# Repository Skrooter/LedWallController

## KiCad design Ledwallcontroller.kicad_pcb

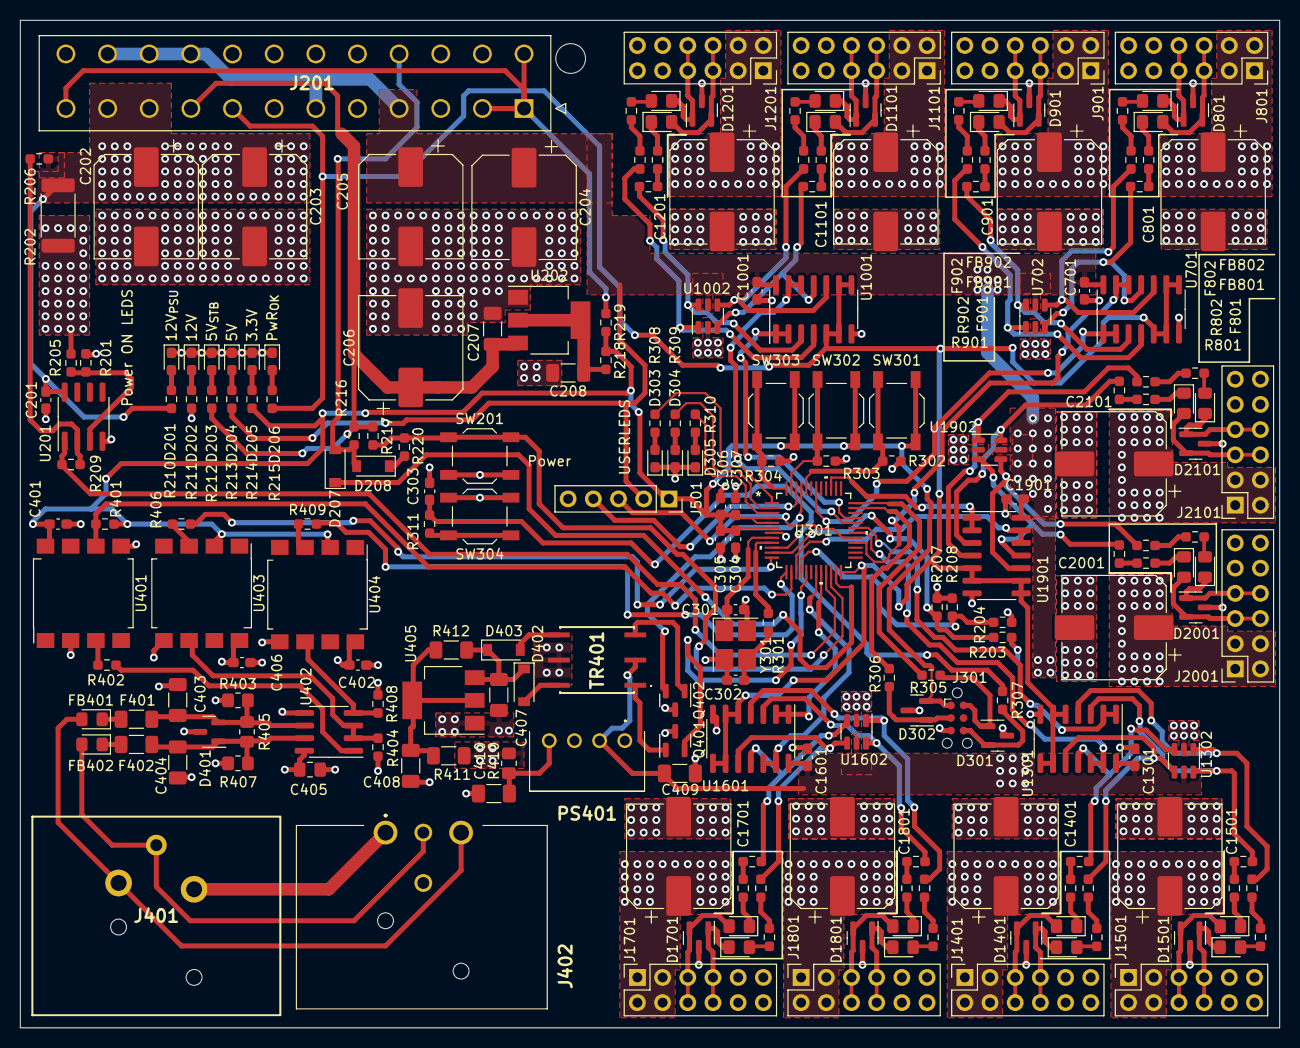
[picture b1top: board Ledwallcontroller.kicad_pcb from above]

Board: 4 copper layers, 127.0 x 101.6 mm, 216 parts (0 on the bottom side), 162 nets.

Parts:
C201, C303, C305, C307, C401, C402, C406, C701, C1001, C1301, C1601, C1901: 100n/50V; C_0603_1608Metric_Pad1.08x0.95mm_HandSolder
C202, C203, C204, C205, C206, C801, C901, C1101, C1201, C1401, C1501, C1701, C1801, C2001, C2101: 220u/50V; CP_Elec_10x10
C207, C208, C407, C408: 22u/25V; C_1206_3216Metric_Pad1.33x1.80mm_HandSolder
C301, C302: 10p/50V; C_0603_1608Metric_Pad1.08x0.95mm_HandSolder
C304: 4u7/16V; C_0603_1608Metric_Pad1.08x0.95mm_HandSolder
C306: 1u/50V; C_0603_1608Metric_Pad1.08x0.95mm_HandSolder
C403, C404: 100p/1kV; C_1206_3216Metric_Pad1.33x1.80mm_HandSolder
C405: 2.2u/50V; C_0805_2012Metric_Pad1.18x1.45mm_HandSolder
C409, C410: 47u/10V; C_1206_3216Metric_Pad1.33x1.80mm_HandSolder
D201, D202, D203, D204, D205, D206: Green; LED_0603_1608Metric_Pad1.05x0.95mm_HandSolder
D207, D208: D; D_SOD-123
D301, D302, D401, D801, D901, D1101, D1201, D1401, D1501, D1701, D1801, D2001, D2101: SM712; SOT-23
D303, D304, D305: Blue; LED_0603_1608Metric_Pad1.05x0.95mm_HandSolder
D402, D403: B5819W; D_SOD-123
F401, F402: Polyfuse_Small; R_1206_3216Metric_Pad1.30x1.75mm_HandSolder
F801, F802, F901, F902, F1101, F1102, F1201, F1202, F1401, F1402, F1501, F1502, F1701, F1702, F1801, F1802, F2001, F2002, F2101, F2102: Polyfuse_Small; R_0603_1608Metric_Pad0.98x0.95mm_HandSolder
FB401, FB402, FB801, FB802, FB901, FB902, FB1101, FB1102, FB1201, FB1202, FB1401, FB1402, FB1501, FB1502, FB1701, FB1702, FB1801, FB1802, FB2001, FB2002, FB2101, FB2102: FerriteBead; D_0805_2012Metric_Pad1.15x1.40mm_HandSolder
J201: ATX-24; 442060007
J301: TC-2030-NL; Tag-Connect_TC2030-IDC-NL_2x03_P1.27mm_Vertical
J401: DMX_{IN}; NC3FAAH0
J402: DMX_{THRU}; NC3MAAH0
J501: Conn_01x06; PinSocket_1x05_P2.54mm_Vertical
J801, J901, J1101, J1201, J1401, J1501, J1701, J1801, J2001, J2101: Conn_02x06_Odd_Even; PinSocket_2x06_P2.54mm_Vertical
PS401: B0505S-1WR3; B0505SW2R2
Q401, Q402: AO3400A; SOT-23
R201, R209: 300k; R_0603_1608Metric_Pad0.98x0.95mm_HandSolder
R202: 10m; R_2512_6332Metric_Pad1.40x3.35mm_HandSolder
R203, R205, R206, R208: 10k; R_0603_1608Metric_Pad0.98x0.95mm_HandSolder
R204: 30k; R_0603_1608Metric_Pad0.98x0.95mm_HandSolder
R207: 15k; R_0603_1608Metric_Pad0.98x0.95mm_HandSolder
R210, R211, R302, R303, R304, R311: 2k2; R_0603_1608Metric_Pad0.98x0.95mm_HandSolder
R212, R213, R215: 820R; R_0603_1608Metric_Pad0.98x0.95mm_HandSolder
R214, R308, R309, R310, R401, R404, R408: 470R; R_0603_1608Metric_Pad0.98x0.95mm_HandSolder
R216, R217: 4k7; R_0603_1608Metric_Pad0.98x0.95mm_HandSolder
R218: 0R; R_0603_1608Metric_Pad0.98x0.95mm_HandSolder
R219, R220: 0R/NM; R_0603_1608Metric_Pad0.98x0.95mm_HandSolder
R301, R305, R306, R307, R801, R802, R901, R902, R1101, R1102, R1201, R1202, R1401, R1402, R1501, R1502, R1701, R1702, R1801, R1802, R2001, R2002, R2101, R2102: 22R; R_0603_1608Metric_Pad0.98x0.95mm_HandSolder
R402: 330R; R_0603_1608Metric_Pad0.98x0.95mm_HandSolder
R403, R407: 680R; R_0805_2012Metric_Pad1.20x1.40mm_HandSolder
R405: 100R/NM; R_0805_2012Metric_Pad1.20x1.40mm_HandSolder
R406, R409: 220R; R_0603_1608Metric_Pad0.98x0.95mm_HandSolder
R410: 0R; R_0805_2012Metric_Pad1.20x1.40mm_HandSolder
R411, R412: 0R/NM; R_1206_3216Metric_Pad1.30x1.75mm_HandSolder
SW201: NM; SW_SPST_TL3342
SW301, SW302, SW303, SW304: SW_MEC_5G; SW_SPST_TL3342
TR401: VPT85BB-01A; VPT85BB01A
U201: OPA2197xD; SOIC-8_3.9x4.9mm_P1.27mm
U202: AMS1117-3.3; SOT-223-3_TabPin2
U301: STM32G030C8T6; LQFP48
U401, U403, U404: 6N137; SSO-8_6.7x9.8mm_P2.54mm_Clearance8mm
U402: SN65176B; SOIC-8_3.9x4.9mm_P1.27mm
U405: AMS1117-5.0; SOT-223-3_TabPin2
U701, U1001, U1301, U1601, U1901: 74HC08D; SOIC-14_3.9x8.7mm_P1.27mm
U702, U1002, U1302, U1602, U1902: SRV05-4; SOT-23-6
Y301: 16MHz; Crystal_SMD_3225-4Pin_3.2x2.5mm_HandSoldering

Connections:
+3.3V: C304.1, C305.2, C306.1, C307.1, C401.2, D302.2 (A2), J301.1, J501.1, R214.2, R218.1, R219.2, R401.2, SW301.2 (B), SW302.2 (B), SW303.2 (B), U301.4 (VBAT), U301.5 (VREF+), U301.6 (VDD/VDDA), U401.8 (VCC), U403.2 (A), U404.2 (A)
+5V: C204.1, C205.1, C409.2, C701.1, C1001.1, C1301.1, C1601.1, C1901.1, J201.4 (+5V), J201.6 (+5V), J201.21 (+5V), J201.22 (+5V), J201.23 (+5V), J501.2, PS401.2 (+Vin), R203.2, R213.2, TR401.2, U701.14 (VDD), U702.5 (VP), U1001.14 (VDD), U1002.5 (VP), U1301.14 (VDD), U1302.5 (VP), U1601.14 (VDD), U1602.5 (VP), U1901.14 (VDD), U1902.5 (VP)
+12V: C801.1, C901.1, C1101.1, C1201.1, C1401.1, C1501.1, C1701.1, C1801.1, C2001.1, C2101.1, J801.1, J801.2, J801.3, J801.4, J901.1, J901.2, J901.3, J901.4, J1101.1, J1101.2, J1101.3, J1101.4, J1201.1, J1201.2, J1201.3, J1201.4, J1401.1, J1401.2, J1401.3, J1401.4, J1501.1, J1501.2, J1501.3, J1501.4, J1701.1, J1701.2, J1701.3, J1701.4, J1801.1, J1801.2, J1801.3, J1801.4, J2001.1, J2001.2, J2001.3, J2001.4, J2101.1, J2101.2, J2101.3, J2101.4, R202.1, R204.1, R205.2, R211.2
/5V_{MONITOR}: R203.1, R207.1, U301.11 (PA0)
/12V_{Isense}: R209.2, U201.1, U301.21 (PB2)
/12V_{MONITOR}: R204.2, R208.2, U301.16 (PA5)
/Button_{POWER}: R217.2, R220.1, SW201.1 (A), U301.22 (PB10)
/DMX/AMS1117_{5VOUT}: C408.1, R411.2, R412.2, U405.2 (VO)
/DMX/B0505_{OUTPUT}: C410.1, PS401.4 (+Vout), R410.1
/DMX/BUS_{A}: FB401.2, J401.2, J402.2
/DMX/BUS_{B}: FB402.2, J401.3, J402.3
/DMX/DMX_{A}: C403.1, D401.2 (A2), F401.2, R403.2, R405.1, U402.6 (A)
/DMX/DMX_{B}: C404.2, D401.1 (A1), F402.2, R405.2, R407.2, U402.7 (B)
/DMX/ISO5V_{rectified}: C407.1, D402.1 (K), D403.1 (K), R412.1, U405.3 (VI)
/DMX/ISO_{DE}: R404.2, U402.2 (~RE), U402.3 (DE), U403.6 (VO)
/DMX/ISO_{D}: R408.2, U402.4 (D), U404.6 (VO)
/DMX/ISO_{R}: R402.1, U402.1 (R)
/DMX/ISO_{TRAFO1}: D402.2 (A), TR401.6
/DMX/ISO_{TRAFO2}: D403.2 (A), TR401.4
/DMX/OPTO_{DE}: R406.1, U403.3 (C)
/DMX/OPTO_{TX}: R409.1, U404.3 (C)
/DMX/Trafo1prim: Q401.1 (D), TR401.1
/DMX/Trafo2prim: Q402.1 (D), TR401.3
/DMX/U401_{C}: R402.2, U401.3 (C)
/DMX/filtered_{A}: F401.1, FB401.1
/DMX/filtered_{B}: F402.1, FB402.1
/DMX_{DE}: R406.2, U301.12 (PA1)
/DMX_{RX}: R401.1, U301.14 (PA3), U401.6 (VO)
/DMX_{TX}: R409.2, U301.13 (PA2)
/Enable_Power: D207.1 (K), U301.23 (PB11)
/LEDOUT/LEDOUTCELL0/LEDOUTEDGE_{A}/LEDOUT: R801.1, U701.11, U702.3 (IO2)
/LEDOUT/LEDOUTCELL0/LEDOUTEDGE_{A}/LED_{BEAD}: F801.2, FB801.1
/LEDOUT/LEDOUTCELL0/LEDOUTEDGE_{A}/LED_{CONN}: D801.2 (A2), FB801.2, J801.5, J801.6
/LEDOUT/LEDOUTCELL0/LEDOUTEDGE_{A}/LED_{FUSE}: F801.1, R801.2
/LEDOUT/LEDOUTCELL0/LEDOUTEDGE_{A}/PWRENA: R802.1, U701.10, U702.4 (IO3)
/LEDOUT/LEDOUTCELL0/LEDOUTEDGE_{A}/PWR_{BEAD}: F802.1, FB802.2
/LEDOUT/LEDOUTCELL0/LEDOUTEDGE_{A}/PWR_{CONN}: D801.1 (A1), FB802.1, J801.7, J801.8
/LEDOUT/LEDOUTCELL0/LEDOUTEDGE_{A}/PWR_{FUSE}: F802.2, R802.2
/LEDOUT/LEDOUTCELL0/LEDOUTEDGE_{B}/LEDOUT: R901.1, U701.3, U702.6 (IO4)
/LEDOUT/LEDOUTCELL0/LEDOUTEDGE_{B}/LED_{BEAD}: F901.2, FB901.1
/LEDOUT/LEDOUTCELL0/LEDOUTEDGE_{B}/LED_{CONN}: D901.2 (A2), FB901.2, J901.5, J901.6
/LEDOUT/LEDOUTCELL0/LEDOUTEDGE_{B}/LED_{FUSE}: F901.1, R901.2
/LEDOUT/LEDOUTCELL0/LEDOUTEDGE_{B}/PWRENA: R902.1, U701.4, U702.1 (IO1)
/LEDOUT/LEDOUTCELL0/LEDOUTEDGE_{B}/PWR_{BEAD}: F902.1, FB902.2
/LEDOUT/LEDOUTCELL0/LEDOUTEDGE_{B}/PWR_{CONN}: D901.1 (A1), FB902.1, J901.7, J901.8
/LEDOUT/LEDOUTCELL0/LEDOUTEDGE_{B}/PWR_{FUSE}: F902.2, R902.2
/LEDOUT/LEDOUTCELL1/LEDOUTEDGE_{A}/LEDOUT: R1101.1, U1001.11, U1002.3 (IO2)
/LEDOUT/LEDOUTCELL1/LEDOUTEDGE_{A}/LED_{BEAD}: F1101.2, FB1101.1
/LEDOUT/LEDOUTCELL1/LEDOUTEDGE_{A}/LED_{CONN}: D1101.2 (A2), FB1101.2, J1101.5, J1101.6
/LEDOUT/LEDOUTCELL1/LEDOUTEDGE_{A}/LED_{FUSE}: F1101.1, R1101.2
/LEDOUT/LEDOUTCELL1/LEDOUTEDGE_{A}/PWRENA: R1102.1, U1001.10, U1002.4 (IO3)
/LEDOUT/LEDOUTCELL1/LEDOUTEDGE_{A}/PWR_{BEAD}: F1102.1, FB1102.2
/LEDOUT/LEDOUTCELL1/LEDOUTEDGE_{A}/PWR_{CONN}: D1101.1 (A1), FB1102.1, J1101.7, J1101.8
/LEDOUT/LEDOUTCELL1/LEDOUTEDGE_{A}/PWR_{FUSE}: F1102.2, R1102.2
/LEDOUT/LEDOUTCELL1/LEDOUTEDGE_{B}/LEDOUT: R1201.1, U1001.3, U1002.6 (IO4)
/LEDOUT/LEDOUTCELL1/LEDOUTEDGE_{B}/LED_{BEAD}: F1201.2, FB1201.1
/LEDOUT/LEDOUTCELL1/LEDOUTEDGE_{B}/LED_{CONN}: D1201.2 (A2), FB1201.2, J1201.5, J1201.6
/LEDOUT/LEDOUTCELL1/LEDOUTEDGE_{B}/LED_{FUSE}: F1201.1, R1201.2
/LEDOUT/LEDOUTCELL1/LEDOUTEDGE_{B}/PWRENA: R1202.1, U1001.4, U1002.1 (IO1)
/LEDOUT/LEDOUTCELL1/LEDOUTEDGE_{B}/PWR_{BEAD}: F1202.1, FB1202.2
/LEDOUT/LEDOUTCELL1/LEDOUTEDGE_{B}/PWR_{CONN}: D1201.1 (A1), FB1202.1, J1201.7, J1201.8
/LEDOUT/LEDOUTCELL1/LEDOUTEDGE_{B}/PWR_{FUSE}: F1202.2, R1202.2
/LEDOUT/LEDOUTCELL2/LEDOUTEDGE_{A}/LEDOUT: R1401.1, U1301.11, U1302.3 (IO2)
/LEDOUT/LEDOUTCELL2/LEDOUTEDGE_{A}/LED_{BEAD}: F1401.2, FB1401.1
/LEDOUT/LEDOUTCELL2/LEDOUTEDGE_{A}/LED_{CONN}: D1401.2 (A2), FB1401.2, J1401.5, J1401.6
/LEDOUT/LEDOUTCELL2/LEDOUTEDGE_{A}/LED_{FUSE}: F1401.1, R1401.2
/LEDOUT/LEDOUTCELL2/LEDOUTEDGE_{A}/PWRENA: R1402.1, U1301.10, U1302.4 (IO3)
/LEDOUT/LEDOUTCELL2/LEDOUTEDGE_{A}/PWR_{BEAD}: F1402.1, FB1402.2
/LEDOUT/LEDOUTCELL2/LEDOUTEDGE_{A}/PWR_{CONN}: D1401.1 (A1), FB1402.1, J1401.7, J1401.8
/LEDOUT/LEDOUTCELL2/LEDOUTEDGE_{A}/PWR_{FUSE}: F1402.2, R1402.2
/LEDOUT/LEDOUTCELL2/LEDOUTEDGE_{B}/LEDOUT: R1501.1, U1301.3, U1302.6 (IO4)
/LEDOUT/LEDOUTCELL2/LEDOUTEDGE_{B}/LED_{BEAD}: F1501.2, FB1501.1
/LEDOUT/LEDOUTCELL2/LEDOUTEDGE_{B}/LED_{CONN}: D1501.2 (A2), FB1501.2, J1501.5, J1501.6
/LEDOUT/LEDOUTCELL2/LEDOUTEDGE_{B}/LED_{FUSE}: F1501.1, R1501.2
/LEDOUT/LEDOUTCELL2/LEDOUTEDGE_{B}/PWRENA: R1502.1, U1301.4, U1302.1 (IO1)
/LEDOUT/LEDOUTCELL2/LEDOUTEDGE_{B}/PWR_{BEAD}: F1502.1, FB1502.2
/LEDOUT/LEDOUTCELL2/LEDOUTEDGE_{B}/PWR_{CONN}: D1501.1 (A1), FB1502.1, J1501.7, J1501.8
/LEDOUT/LEDOUTCELL2/LEDOUTEDGE_{B}/PWR_{FUSE}: F1502.2, R1502.2
/LEDOUT/LEDOUTCELL3/LEDOUTEDGE_{A}/LEDOUT: R1701.1, U1601.11, U1602.3 (IO2)
/LEDOUT/LEDOUTCELL3/LEDOUTEDGE_{A}/LED_{BEAD}: F1701.2, FB1701.1
/LEDOUT/LEDOUTCELL3/LEDOUTEDGE_{A}/LED_{CONN}: D1701.2 (A2), FB1701.2, J1701.5, J1701.6
/LEDOUT/LEDOUTCELL3/LEDOUTEDGE_{A}/LED_{FUSE}: F1701.1, R1701.2
/LEDOUT/LEDOUTCELL3/LEDOUTEDGE_{A}/PWRENA: R1702.1, U1601.10, U1602.4 (IO3)
/LEDOUT/LEDOUTCELL3/LEDOUTEDGE_{A}/PWR_{BEAD}: F1702.1, FB1702.2
/LEDOUT/LEDOUTCELL3/LEDOUTEDGE_{A}/PWR_{CONN}: D1701.1 (A1), FB1702.1, J1701.7, J1701.8
/LEDOUT/LEDOUTCELL3/LEDOUTEDGE_{A}/PWR_{FUSE}: F1702.2, R1702.2
/LEDOUT/LEDOUTCELL3/LEDOUTEDGE_{B}/LEDOUT: R1801.1, U1601.3, U1602.6 (IO4)
/LEDOUT/LEDOUTCELL3/LEDOUTEDGE_{B}/LED_{BEAD}: F1801.2, FB1801.1
/LEDOUT/LEDOUTCELL3/LEDOUTEDGE_{B}/LED_{CONN}: D1801.2 (A2), FB1801.2, J1801.5, J1801.6
/LEDOUT/LEDOUTCELL3/LEDOUTEDGE_{B}/LED_{FUSE}: F1801.1, R1801.2
/LEDOUT/LEDOUTCELL3/LEDOUTEDGE_{B}/PWRENA: R1802.1, U1601.4, U1602.1 (IO1)
/LEDOUT/LEDOUTCELL3/LEDOUTEDGE_{B}/PWR_{BEAD}: F1802.1, FB1802.2
/LEDOUT/LEDOUTCELL3/LEDOUTEDGE_{B}/PWR_{CONN}: D1801.1 (A1), FB1802.1, J1801.7, J1801.8
/LEDOUT/LEDOUTCELL3/LEDOUTEDGE_{B}/PWR_{FUSE}: F1802.2, R1802.2
/LEDOUT/LEDOUTCELL4/LEDOUTEDGE_{A}/LEDOUT: R2001.1, U1901.11, U1902.3 (IO2)
/LEDOUT/LEDOUTCELL4/LEDOUTEDGE_{A}/LED_{BEAD}: F2001.2, FB2001.1
/LEDOUT/LEDOUTCELL4/LEDOUTEDGE_{A}/LED_{CONN}: D2001.2 (A2), FB2001.2, J2001.5, J2001.6
/LEDOUT/LEDOUTCELL4/LEDOUTEDGE_{A}/LED_{FUSE}: F2001.1, R2001.2
/LEDOUT/LEDOUTCELL4/LEDOUTEDGE_{A}/PWRENA: R2002.1, U1901.10, U1902.4 (IO3)
/LEDOUT/LEDOUTCELL4/LEDOUTEDGE_{A}/PWR_{BEAD}: F2002.1, FB2002.2
/LEDOUT/LEDOUTCELL4/LEDOUTEDGE_{A}/PWR_{CONN}: D2001.1 (A1), FB2002.1, J2001.7, J2001.8
/LEDOUT/LEDOUTCELL4/LEDOUTEDGE_{A}/PWR_{FUSE}: F2002.2, R2002.2
/LEDOUT/LEDOUTCELL4/LEDOUTEDGE_{B}/LEDOUT: R2101.1, U1901.3, U1902.6 (IO4)
/LEDOUT/LEDOUTCELL4/LEDOUTEDGE_{B}/LED_{BEAD}: F2101.2, FB2101.1
/LEDOUT/LEDOUTCELL4/LEDOUTEDGE_{B}/LED_{CONN}: D2101.2 (A2), FB2101.2, J2101.5, J2101.6
/LEDOUT/LEDOUTCELL4/LEDOUTEDGE_{B}/LED_{FUSE}: F2101.1, R2101.2
/LEDOUT/LEDOUTCELL4/LEDOUTEDGE_{B}/PWRENA: R2102.1, U1901.4, U1902.1 (IO1)
/LEDOUT/LEDOUTCELL4/LEDOUTEDGE_{B}/PWR_{BEAD}: F2102.1, FB2102.2
/LEDOUT/LEDOUTCELL4/LEDOUTEDGE_{B}/PWR_{CONN}: D2101.1 (A1), FB2102.1, J2101.7, J2101.8
/LEDOUT/LEDOUTCELL4/LEDOUTEDGE_{B}/PWR_{FUSE}: F2102.2, R2102.2
/LEDOUT_{0}: U301.28 (PA8), U701.12, U701.13
/LEDOUT_{1}: U301.42 (PB3), U701.1, U701.2
/LEDOUT_{2}: U301.32 (PA10), U1001.12, U1001.13
/LEDOUT_{3}: U301.33 (PA11), U1001.1, U1001.2
/LEDOUT_{4}: U301.30 (PC6), U1301.12, U1301.13
/LEDOUT_{5}: U301.31 (PC7), U1301.1, U1301.2
/LEDOUT_{6}: U301.19 (PB0), U1601.12, U1601.13
/LEDOUT_{7}: U301.20 (PB1), U1601.1, U1601.2
/LEDOUT_{8}: U301.15 (PA4), U1901.12, U1901.13
/LEDOUT_{9}: U301.39 (PD1), U1901.1, U1901.2
/MCU/BTN_{1}: R302.1, SW301.1 (A), U301.44 (PB5)
/MCU/BTN_{2}: R303.1, SW302.1 (A), U301.47 (PB8)
/MCU/BTN_{3}: R304.1, SW303.1 (A), U301.48 (PB9)
/MCU/LED_{1}: D303.2 (A), R308.2
/MCU/LED_{2}: D304.2 (A), R309.2
/MCU/LED_{3}: D305.2 (A), R310.2
/MCU/MCU_SWD_{CLK}: R305.2, U301.36 (PA14-BOOT0)
/MCU/MCU_SWD_{DIO}: R306.1, U301.35 (PA13)
/MCU/NRST_{BTN}: R311.2, SW304.2 (B)
/MCU/NRST_{MCU}: C303.2, R307.1, R311.1, U301.10 (NRST)
/MCU/NRST_{debug}: D301.2 (A2), J301.6, R307.2
/MCU/OSC_{IN}: C301.2, U301.8 (PF0-OSC_IN), Y301.1
/MCU/OSC_{OUT}: R301.2, U301.9 (PF1-OSC_OUT)
/MCU/SWD_{CLK}: D302.1 (A1), J301.3, R306.2
/MCU/SWD_{DIO}: D301.1 (A1), J301.2, R305.1
/MCU/USERLED_{1}: R308.1, U301.1 (PC13)
/MCU/USERLED_{2}: R309.1, U301.2 (PC14-OSC32_IN)
/MCU/USERLED_{3}: R310.1, U301.3 (PC15-OSC32_OUT)
/MCU/XTAL_{IN}: C302.1, R301.1, Y301.3
/MIDI_{RX}: J501.4, U301.46 (PB7)
/MIDI_{TX}: J501.3, U301.29 (PA9)
/PWR_{OK}: J201.8 (PWR_OK), R215.2, U301.24 (PB12), U701.5, U701.6, U701.8, U701.9, U1001.5, U1001.6, U1001.8, U1001.9, U1301.5, U1301.6, U1301.8, U1301.9, U1601.5, U1601.6, U1601.8, U1601.9, U1901.5, U1901.6, U1901.8, U1901.9
/Power/3V3_{PSU}: J201.1 (+3.3V), J201.2 (+3.3V), J201.12 (+3.3V), J201.13 (+3.3V), R219.1
/Power/3V3_{regulator}: C208.1, R218.2, U202.2 (VO)
/Power/5V_{STB}: C206.1, C207.2, J201.9 (+5VSB), R212.2, R216.1, R217.1, U202.3 (VI)
/Power/12V_{PSU}: C201.2, C202.1, C203.1, J201.10 (+12V), J201.11 (+12V), R202.2, R206.1, R210.2, U201.8 (V+)
/Power/OP+_{Current}: R201.2, R205.1, U201.3 (+)
/Power/OP-_{Current}: R206.2, R209.1, U201.2 (-)
/Power/PS_{ON}: D207.2 (A), D208.2 (A), J201.16 (PS_ON#), R216.2
/Power/PS_{select}: D208.1 (K), R220.2
/Power/PWRLED_{1}: D201.2 (A), R210.1
/Power/PWRLED_{2}: D202.2 (A), R211.1
/Power/PWRLED_{3}: D203.2 (A), R212.1
/Power/PWRLED_{4}: D204.2 (A), R213.1
/Power/PWRLED_{5}: D205.2 (A), R214.1
/Power/PWRLED_{6}: D206.2 (A), R215.1
/Trafo1: Q401.2 (G), U301.17 (PA6)
/Trafo2: Q402.2 (G), U301.45 (PB6)
GND: C201.1, C202.2, C203.2, C204.2, C205.2, C206.2, C207.1, C208.2, C301.1, C302.2, C303.1, C304.2, C305.1, C306.2, C307.2, C401.1, C409.1, C701.2, C801.2, C901.2, C1001.2, C1101.2, C1201.2, C1301.2, C1401.2, C1501.2, C1601.2, C1701.2, C1801.2, C1901.2, C2001.2, C2101.2, D201.1 (K), D202.1 (K), D203.1 (K), D204.1 (K), D205.1 (K), D206.1 (K), D301.3 (common), D302.3 (common), D303.1 (K), D304.1 (K), D305.1 (K), D801.3 (common), D901.3 (common), D1101.3 (common), D1201.3 (common), D1401.3 (common), D1501.3 (common), D1701.3 (common), D1801.3 (common), D2001.3 (common), D2101.3 (common), J201.3 (GND), J201.5 (GND), J201.7 (GND), J201.15 (GND), J201.17 (GND), J201.18 (GND), J201.19 (GND), J201.24 (GND), J301.5, J501.5, J801.9, J801.10, J801.11, J801.12, J901.9, J901.10, J901.11, J901.12, J1101.9, J1101.10, J1101.11, J1101.12, J1201.9, J1201.10, J1201.11, J1201.12, J1401.9, J1401.10, J1401.11, J1401.12, J1501.9, J1501.10, J1501.11, J1501.12, J1701.9, J1701.10, J1701.11, J1701.12, J1801.9, J1801.10, J1801.11, J1801.12, J2001.9, J2001.10, J2001.11, J2001.12, J2101.9, J2101.10, J2101.11, J2101.12, PS401.1 (-Vin), Q401.3 (S), Q402.3 (S), R201.1, R207.2, R208.1, R302.2, R303.2, R304.2, SW201.2 (B), SW304.1 (A), U201.4 (V-), U202.1 (GND), U301.7 (VSS/VSSA), U401.5 (GND), U701.7 (VSS), U702.2 (VN), U1001.7 (VSS), U1002.2 (VN), U1301.7 (VSS), U1302.2 (VN), U1601.7 (VSS), U1602.2 (VN), U1901.7 (VSS), U1902.2 (VN), Y301.2, Y301.4
ISOGND: C402.1, C403.2, C404.1, C405.2, C406.2, C407.2, C408.2, C410.2, D401.3 (common), PS401.3 (-Vout), R407.1, TR401.5, U402.5 (GND), U403.5 (GND), U404.5 (GND), U405.1 (GND)
ISOVCC: C402.2, C405.1, C406.1, R403.1, R404.1, R408.1, R410.2, R411.1, U401.2 (A), U402.8 (V_{CC}), U403.8 (VCC), U404.8 (VCC)
SHIELD: J401.1, J402.1

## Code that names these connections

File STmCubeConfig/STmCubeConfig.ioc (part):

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Mcu.Name=STM32G030C(6-8)Tx
Mcu.Package=LQFP48
Mcu.UserName=STM32G030C8Tx
PA0.GPIOParameters=GPIO_Label
PA0.GPIO_Label=V_5V
PA0.Mode=IN0
PA0.Signal=ADC1_IN0
PA1.GPIOParameters=GPIO_Label
PA1.GPIO_Label=DMX_DE
PA1.Mode=Hardware Flow Control (RS485)
PA1.Signal=USART2_DE
PA10.GPIOParameters=GPIO_Label
PA10.GPIO_Label=LEDOUT2
PA10.Signal=S_TIM1_CH3
PA11\ [PA9].GPIOParameters=GPIO_Label
PA11\ [PA9].GPIO_Label=LEDOUT3
PA11\ [PA9].Signal=S_TIM1_CH4
PA13.Mode=Serial_Wire
PA13.Signal=SYS_SWDIO
PA14-BOOT0.Mode=Serial_Wire
PA14-BOOT0.Signal=SYS_SWCLK
PA2.GPIOParameters=GPIO_Label
PA2.GPIO_Label=DMX_TX
PA2.Mode=Asynchronous
PA2.Signal=USART2_TX
PA3.GPIOParameters=GPIO_Label
PA3.GPIO_Label=DMX_RX
PA3.Mode=Asynchronous
PA3.Signal=USART2_RX
PA4.GPIOParameters=GPIO_Label
PA4.GPIO_Label=LEDOUT8
PA4.Signal=S_TIM14_CH1
PA5.GPIOParameters=GPIO_Label
PA5.GPIO_Label=V_12V
PA5.Mode=IN5
PA5.Signal=ADC1_IN5
PA6.GPIOParameters=GPIO_Label
PA6.GPIO_Label=Trafo1
PA6.Signal=S_TIM16_CH1
PA8.GPIOParameters=GPIO_Label
PA8.GPIO_Label=LEDOUT0
PA8.Signal=S_TIM1_CH1
PA9.GPIOParameters=GPIO_Label
PA9.GPIO_Label=MIDI_TX
PA9.Mode=Asynchronous
PA9.Signal=USART1_TX
PB0.GPIOParameters=GPIO_Label
PB0.GPIO_Label=LEDOUT6
PB0.Signal=S_TIM3_CH3
PB1.GPIOParameters=GPIO_Label
PB1.GPIO_Label=LEDOUT7
PB1.Signal=S_TIM3_CH4
PB10.GPIOParameters=GPIO_Label
PB10.GPIO_Label=BUTTON_POWER
PB10.Signal=GPIO_Input
PB11.GPIOParameters=GPIO_Label
PB11.GPIO_Label=Enable_Power
PB11.Signal=GPIO_Output
PB12.GPIOParameters=GPIO_Label
PB12.GPIO_Label=PWR_OK
PB12.Signal=GPIO_Input
PB2.GPIOParameters=GPIO_Label
PB2.GPIO_Label=I_12V
PB2.Mode=IN10
PB2.Signal=ADC1_IN10
PB3.GPIOParameters=GPIO_Label
PB3.GPIO_Label=LEDOUT1
PB3.Signal=S_TIM1_CH2
PB5.GPIOParameters=GPIO_Label
PB5.GPIO_Label=BTN1
PB5.Signal=GPIO_Input
PB6.GPIOParameters=GPIO_Label
PB6.GPIO_Label=Trafo2
PB6.Mode=Output Compare1 CH1 CH1N
PB6.Signal=TIM16_CH1N
PB7.GPIOParameters=GPIO_Label
PB7.GPIO_Label=MIDI_RX
PB7.Mode=Asynchronous
PB7.Signal=USART1_RX
PB8.GPIOParameters=GPIO_Label
PB8.GPIO_Label=BTN2
PB8.Signal=GPIO_Input
PB9.GPIOParameters=GPIO_Label
PB9.GPIO_Label=BTN3
PB9.Signal=GPIO_Input
PC13.GPIOParameters=GPIO_Label
PC13.GPIO_Label=USERLED3
PC13.Signal=GPIO_Output
PC14-OSC32_IN\ (PC14).GPIOParameters=GPIO_Label
PC14-OSC32_IN\ (PC14).GPIO_Label=USERLED2
PC14-OSC32_IN\ (PC14).Signal=GPIO_Output
PC15-OSC32_OUT\ (PC15).GPIOParameters=GPIO_Label
PC15-OSC32_OUT\ (PC15).GPIO_Label=USERLED1
PC15-OSC32_OUT\ (PC15).Signal=GPIO_Output
PC6.GPIOParameters=GPIO_Label
PC6.GPIO_Label=LEDOUT4
PC6.Signal=S_TIM3_CH1
PC7.GPIOParameters=GPIO_Label
PC7.GPIO_Label=LEDOUT5
PC7.Signal=S_TIM3_CH2
PD1.GPIOParameters=GPIO_Label
PD1.GPIO_Label=LEDOUT9
PD1.Signal=S_TIM17_CH1
PF0-OSC_IN\ (PF0).Mode=HSE-External-Oscillator
PF0-OSC_IN\ (PF0).Signal=RCC_OSC_IN
PF1-OSC_OUT\ (PF1).Mode=HSE-External-Oscillator
PF1-OSC_OUT\ (PF1).Signal=RCC_OSC_OUT
RCC.HSE_VALUE=16000000
RCC.SYSCLKFreq_VALUE=64000000
RCC.SYSCLKSource=RCC_SYSCLKSOURCE_PLLCLK
board=custom

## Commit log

2022-08-22 Inital commit
2022-08-22 Add gitignore
2022-08-29 Added Testpoints
    Schematic and PCB updated
    Also probably some other smaller changes that I forgot about
2022-08-29 Fix DRCs and BOM errors
